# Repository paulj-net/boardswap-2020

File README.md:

# boardswap-2020

This repo contains design files for my contribution to the 2019/2020 boardswap series.  More details on our boardswap can be found on the Boldport Club Discord Server.

A little history on the project...  I got my start in electronics building guitar effects kits.  I've always been fascinated by audio and electronics.  This little circuit was orginally going to be a variation of an Atari Punk Console (hence some of the filenames) but it ended up just being a simple little one octave keyboard with a focus on correct pitch.  The circuit is tuned for proper note steps with the pot in the middle position.  Due to the type of circuit employed the steps between keys change as you move farther from the middle position.  It's not perfect, I'd change a few of the pads to make soldering easier.  I'd also spin the pot 180 degrees and experiment with other speakers.  The particular speaker chosen has a resonant frequency that is hit fairly easily as you play the instrument.  My kids love when that happens, I see it as an area for improvement.  In any case I hope you enjoy it!

Design files were all created in KiCad.

Mouser BOM is here:
https://www.mouser.com/ProjectManager/ProjectDetail.aspx?AccessID=b0c3233f29

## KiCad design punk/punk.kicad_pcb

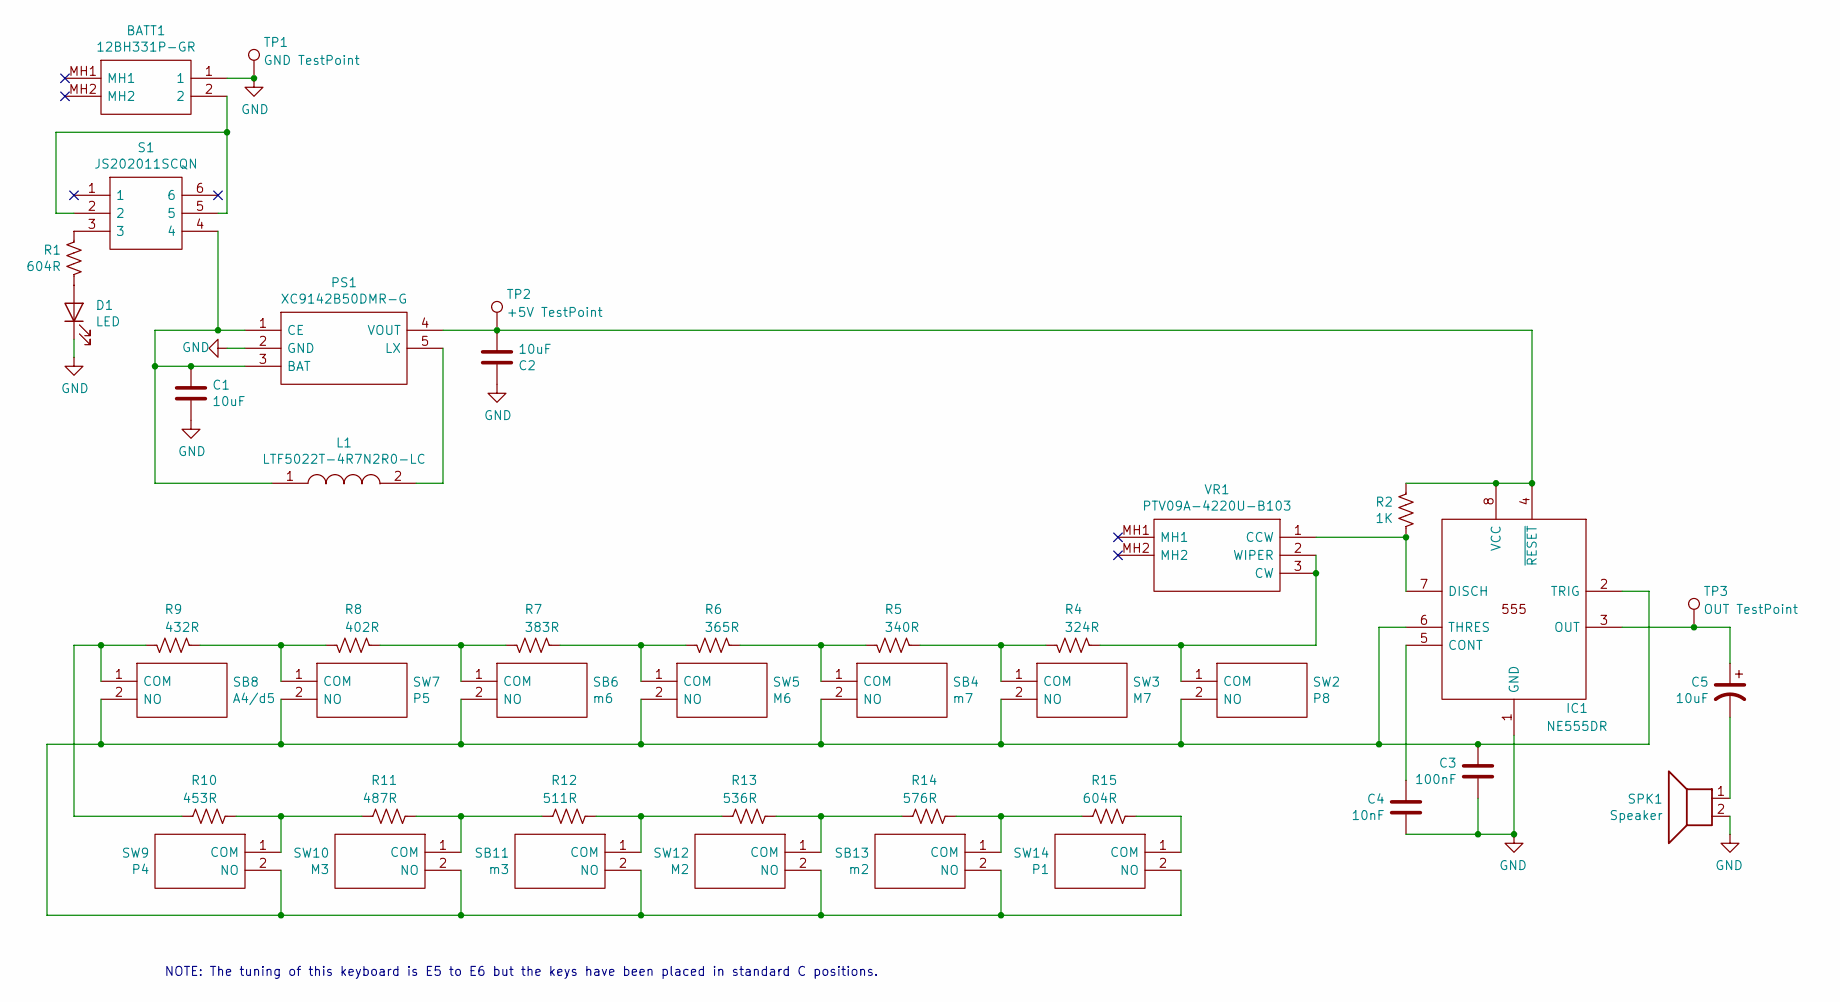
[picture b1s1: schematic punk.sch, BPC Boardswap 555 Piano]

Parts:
BATT1: 12BH331P-GR; 12BH331PGR; Mouser Part Number 12BH331P-GR
C1, C2: 10uF; C_0805_2012Metric_Pad1.15x1.40mm_HandSolder
C3: 100nF; C_0805_2012Metric_Pad1.15x1.40mm_HandSolder
C4: 10nF; C_0805_2012Metric_Pad1.15x1.40mm_HandSolder
C5: 10uF; CP_Elec_4x5.4
D1: LED; LED_1206_3216Metric_Pad1.42x1.75mm_HandSolder
IC1: NE555DR; SOIC127P600X175-8N; Mouser Part Number 595-NE555DR
L1: LTF5022T-4R7N2R0-LC; LTF5022; Mouser Part Number 810-LTF5022T4R7N2R0L
PS1: XC9142B50DMR-G; SOT95P280X120-5N; Mouser Part Number 865-XC9142B50DMR-G
R1, R15: 604R; R_0805_2012Metric_Pad1.15x1.40mm_HandSolder
R2: 1K; R_0805_2012Metric_Pad1.15x1.40mm_HandSolder
R4: 324R; R_0805_2012Metric_Pad1.15x1.40mm_HandSolder
R5: 340R; R_0805_2012Metric_Pad1.15x1.40mm_HandSolder
R6: 365R; R_0805_2012Metric_Pad1.15x1.40mm_HandSolder
R7: 383R; R_0805_2012Metric_Pad1.15x1.40mm_HandSolder
R8: 402R; R_0805_2012Metric_Pad1.15x1.40mm_HandSolder
R9: 432R; R_0805_2012Metric_Pad1.15x1.40mm_HandSolder
R10: 453R; R_0805_2012Metric_Pad1.15x1.40mm_HandSolder
R11: 487R; R_0805_2012Metric_Pad1.15x1.40mm_HandSolder
R12: 511R; R_0805_2012Metric_Pad1.15x1.40mm_HandSolder
R13: 536R; R_0805_2012Metric_Pad1.15x1.40mm_HandSolder
R14: 576R; R_0805_2012Metric_Pad1.15x1.40mm_HandSolder
S1: JS202011SCQN; Mouser Part Number 611-JS202011SCQN
SB4: m7; PTS636SM25SMTRLFS; Mouser Part Number 611-PTS636SM25SMTRLF
SB6: m6; PTS636SM25SMTRLFS; Mouser Part Number 611-PTS636SM25SMTRLF
SB8: A4/d5; PTS636SM25SMTRLFS; Mouser Part Number 611-PTS636SM25SMTRLF
SB11: m3; PTS636SM25SMTRLFS; Mouser Part Number 611-PTS636SM25SMTRLF
SB13: m2; PTS636SM25SMTRLFS; Mouser Part Number 611-PTS636SM25SMTRLF
SPK1: Speaker; TE2507051
SW2: P8; PTS636SM25SMTRLFS; Mouser Part Number 611-PTS636SM25SMTRLF
SW3: M7; PTS636SM25SMTRLFS; Mouser Part Number 611-PTS636SM25SMTRLF
SW5: M6; PTS636SM25SMTRLFS; Mouser Part Number 611-PTS636SM25SMTRLF
SW7: P5; PTS636SM25SMTRLFS; Mouser Part Number 611-PTS636SM25SMTRLF
SW9: P4; PTS636SM25SMTRLFS; Mouser Part Number 611-PTS636SM25SMTRLF
SW10: M3; PTS636SM25SMTRLFS; Mouser Part Number 611-PTS636SM25SMTRLF
SW12: M2; PTS636SM25SMTRLFS; Mouser Part Number 611-PTS636SM25SMTRLF
SW14: P1; PTS636SM25SMTRLFS; Mouser Part Number 611-PTS636SM25SMTRLF
TP1: GND TestPoint; TestPoint_THTPad_2.5x2.5mm_Drill1.2mm
TP2: +5V TestPoint; TestPoint_THTPad_2.5x2.5mm_Drill1.2mm
TP3: OUT TestPoint; TestPoint_THTPad_2.5x2.5mm_Drill1.2mm
VR1: PTV09A-4220U-B103; PTV09A-4#20

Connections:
GND: BATT1.1, C1.2, C2.1, C3.2, C4.2, D1.1 (K), IC1.1 (GND), PS1.2 (GND), SPK1.2, TP1.1; also elsewhere on the board
unnamed: BATT1.2, S1.2, S1.5
unnamed: C1.1, L1.1, PS1.1 (CE), PS1.3 (BAT), S1.4
unnamed 5: C2.2, IC1.4 (~RESET), IC1.8 (VCC), PS1.4 (VOUT), R2.1, TP2.1; also elsewhere on the board
unnamed: C3.1, IC1.2 (TRIG), IC1.6 (THRES), SB4.2 (NO), SB6.2 (NO), SB8.2 (NO), SB11.2 (NO), SB13.2 (NO), SW2.2 (NO), SW3.2 (NO), SW5.2 (NO), SW7.2 (NO), SW9.2 (NO), SW10.2 (NO), SW12.2 (NO), SW14.2 (NO)
unnamed: C4.1, IC1.5 (CONT)
unnamed 8: C5.1, IC1.3 (OUT), TP3.1; also elsewhere on the board
unnamed: C5.2, SPK1.1
unnamed: D1.2 (A), R1.2
unnamed: IC1.7 (DISCH), R2.2, VR1.1 (CCW)
unnamed: L1.2, PS1.5 (LX)
unnamed: R1.1, S1.3
unnamed: R4.1, SW2.1 (COM), VR1.2 (WIPER), VR1.3 (CW)
unnamed: R4.2, R5.1, SW3.1 (COM)
unnamed: R5.2, R6.1, SB4.1 (COM)
unnamed: R6.2, R7.1, SW5.1 (COM)
unnamed: R7.2, R8.1, SB6.1 (COM)
unnamed: R8.2, R9.1, SW7.1 (COM)
unnamed: R9.2, R10.1, SB8.1 (COM)
unnamed: R10.2, R11.1, SW9.1 (COM)
unnamed: R11.2, R12.1, SW10.1 (COM)
unnamed: R12.2, R13.1, SB11.1 (COM)
unnamed: R13.2, R14.1, SW12.1 (COM)
unnamed: R14.2, R15.1, SB13.1 (COM)
unnamed: R15.2, SW14.1 (COM)

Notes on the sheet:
NOTE: The tuning of this keyboard is E5 to E6 but the keys have been placed in standard C positions.

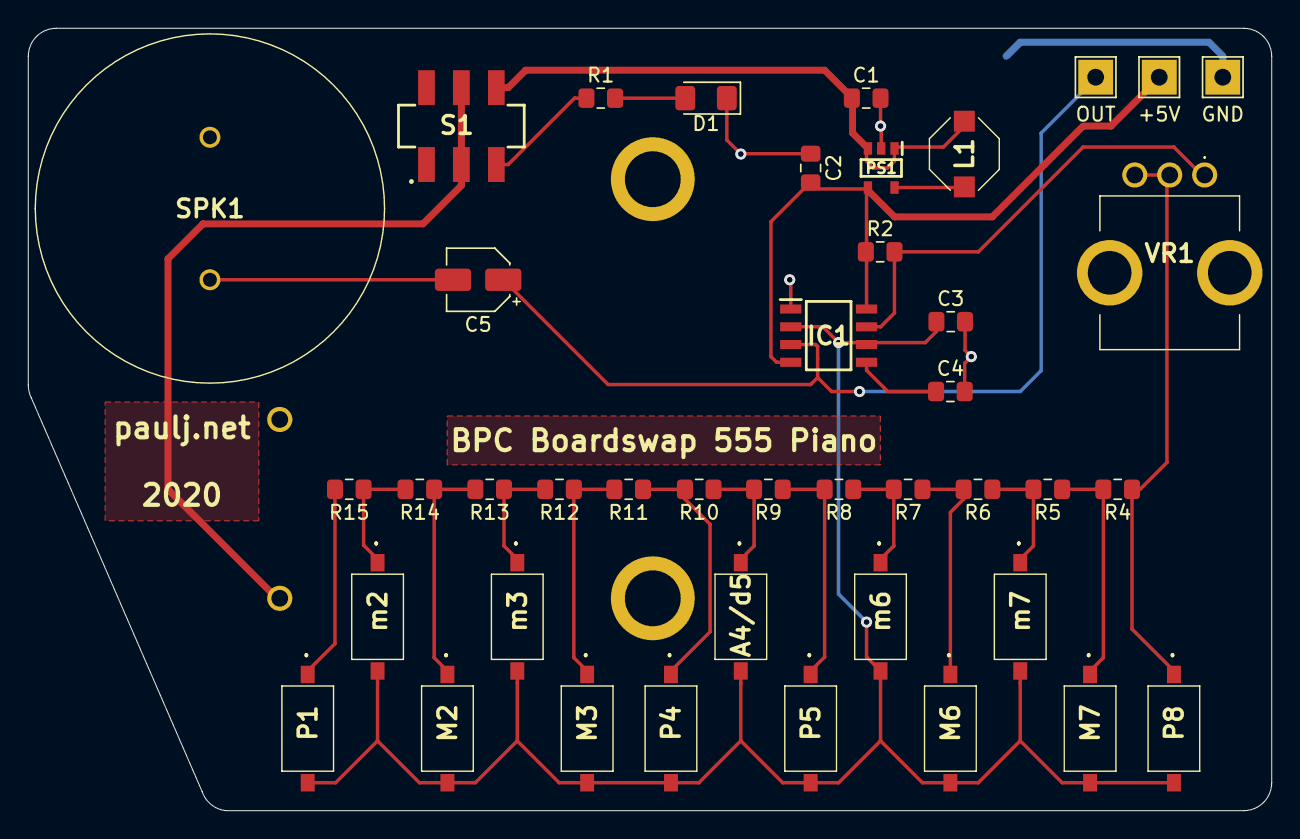
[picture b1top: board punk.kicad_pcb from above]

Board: 2 copper layers, 89.0 x 56.0 mm, 43 parts (1 on the bottom side), 25 nets.

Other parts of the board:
+5V: +5V TestPoint; TestPoint_THTPad_2.5x2.5mm_Drill1.2mm
GND: GND TestPoint; TestPoint_THTPad_2.5x2.5mm_Drill1.2mm
OUT: OUT TestPoint; TestPoint_THTPad_2.5x2.5mm_Drill1.2mm

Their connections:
GND: GND.1; also elsewhere on the board
unnamed 5: +5V.1; also elsewhere on the board
unnamed 8: OUT.1; also elsewhere on the board
